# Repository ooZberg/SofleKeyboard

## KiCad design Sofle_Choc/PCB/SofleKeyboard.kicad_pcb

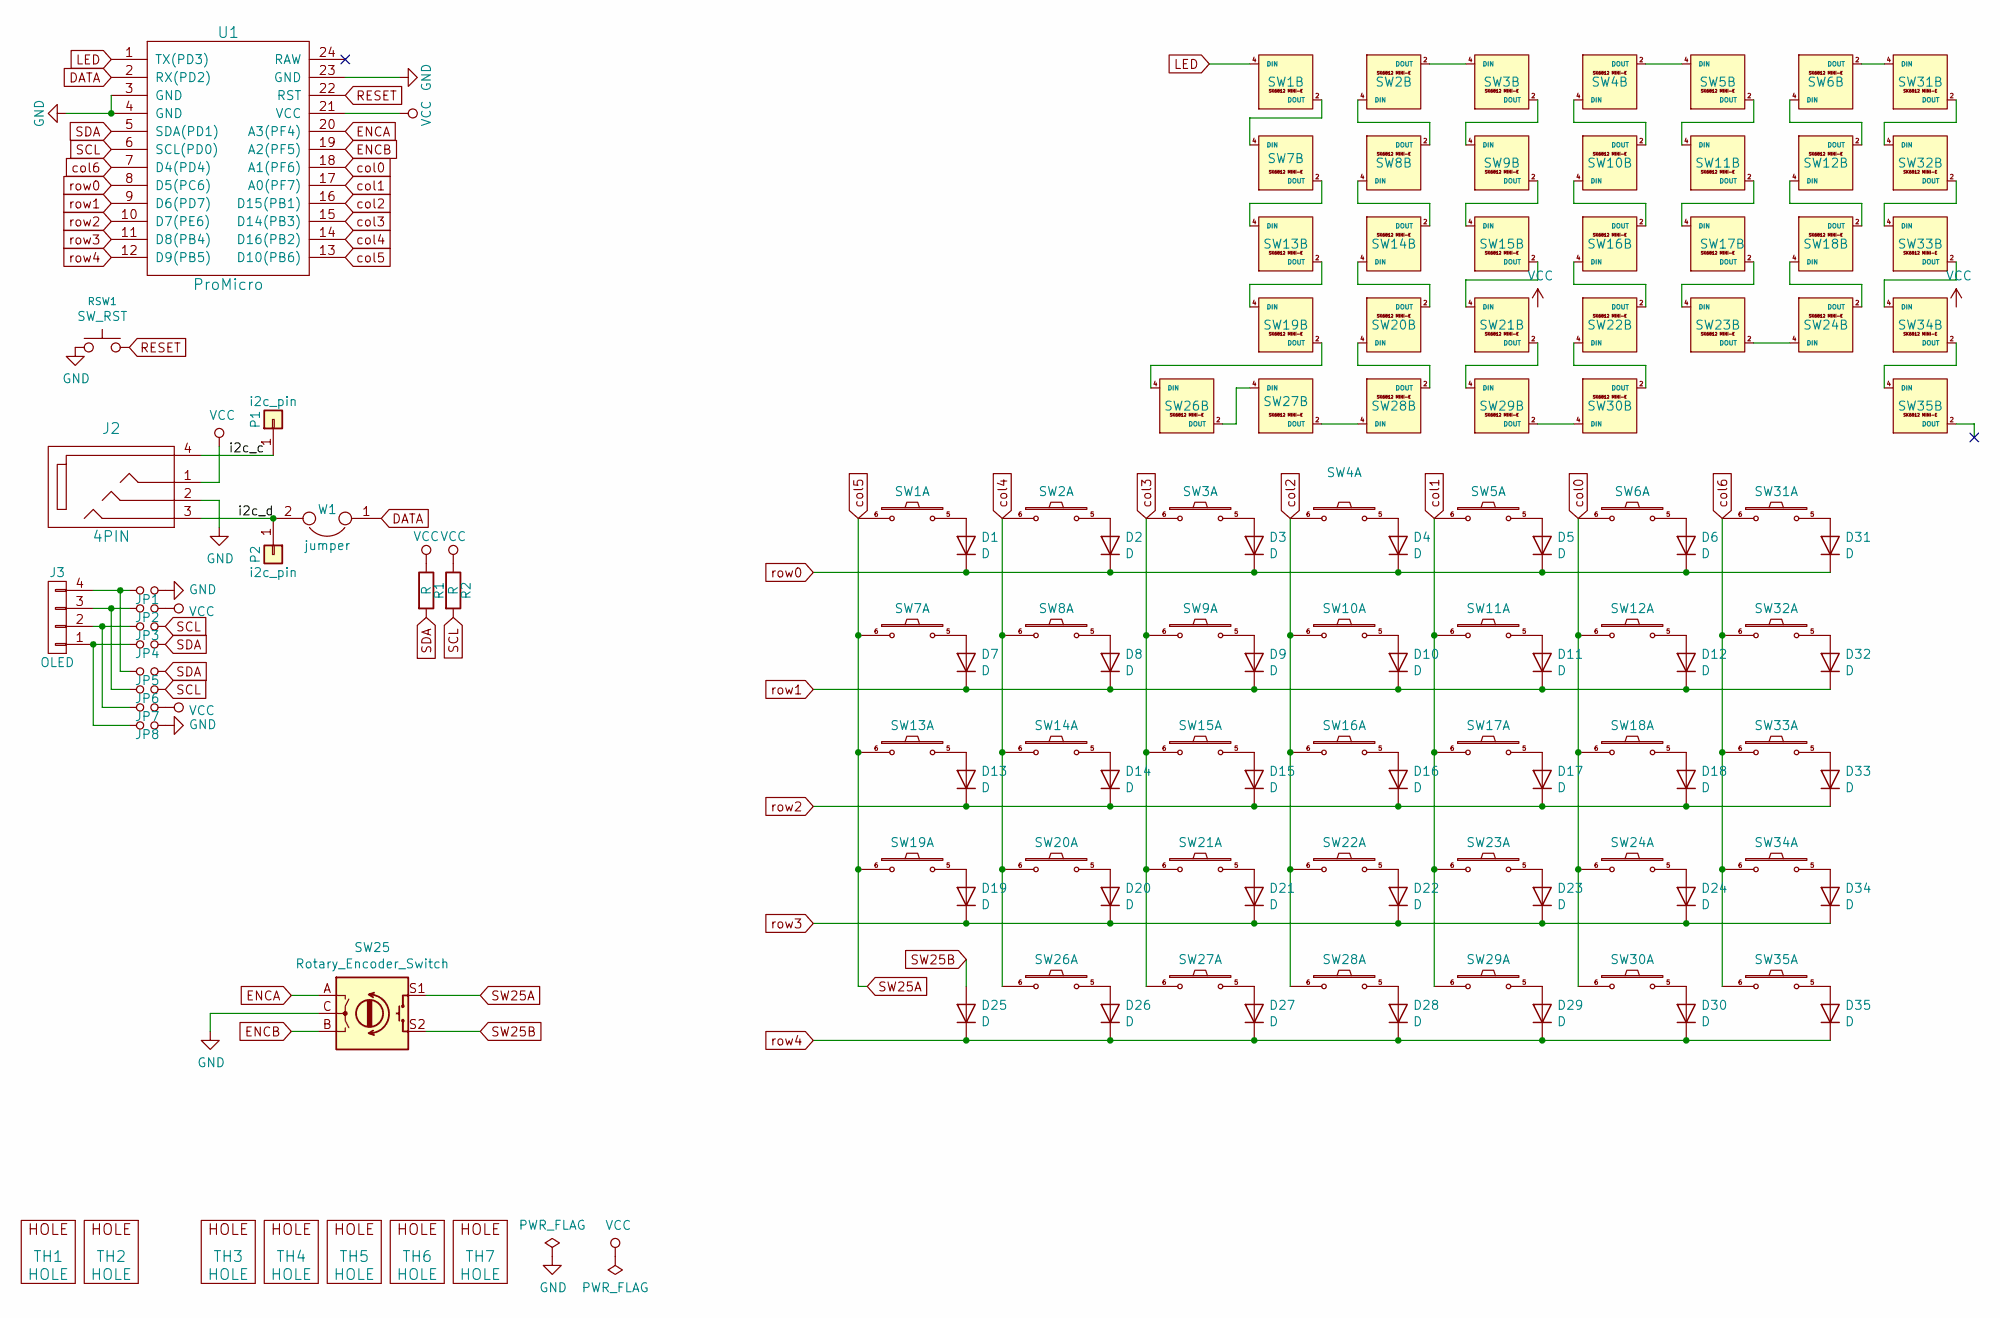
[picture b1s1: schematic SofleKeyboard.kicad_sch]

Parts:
D1, D2, D3, D4, D5, D6, D7, D8, D9, D10, D11, D12, D13, D14, D15, D16, D17, D18, D19, D20, D21, D22, D23, D24, D25, D26, D27, D28, D29, D30, D31, D32, D33, D34, D35: D; Diode_SOD123
J2: 4PIN; MJ-4PP-9
J3: OLED; OLED_4Pin
JP1, JP2, JP3, JP4, JP5, JP6, JP7, JP8: Jumper_NO_Small; Jumper
P1, P2: i2c_pin; 1pin_conn
R1, R2: R; RESISTOR_mini
RSW1: SW_RST; TACT_SWITCH_TVBP06
SW1, SW2, SW3, SW4, SW5, SW6, SW7, SW8, SW9, SW10, SW11, SW12, SW13, SW14, SW15, SW16, SW17, SW18, SW19, SW20, SW21, SW22, SW23, SW24, SW26, SW27, SW28, SW29, SW30, SW31, SW32, SW33, SW34, SW35: SW_PUSH_LED; Choc_Hotswap_SK6812MiniE
SW25: Rotary_Encoder_Switch; RotaryEncoder_Alps_EC11E-Switch_Vertical_H20mm-keebio_modif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
TH1, TH2: HOLE; M2_HOLE_PCB
TH3, TH4, TH5, TH6, TH7: HOLE; HOLE_M2_TH
U1: ProMicro
W1: jumper; jumper_data

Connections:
/i2c_c: J2.4, P1.1
/i2c_d: J2.3, P2.1, W1.2
DATA: U1.2 (RX(PD2)), W1.1
ENCA: SW25.A, U1.20 (A3(PF4))
ENCB: SW25.B, U1.19 (A2(PF5))
GND: J2.2, JP1.2, JP8.2, RSW1.1, SW1.3 (GND), SW2.3 (GND), SW3.3 (GND), SW4.3 (GND), SW5.3 (GND), SW6.3 (GND), SW7.3 (GND), SW8.3 (GND), SW9.3 (GND), SW10.3 (GND), SW11.3 (GND), SW12.3 (GND), SW13.3 (GND), SW14.3 (GND), SW15.3 (GND), SW16.3 (GND), SW17.3 (GND), SW18.3 (GND), SW19.3 (GND), SW20.3 (GND), SW21.3 (GND), SW22.3 (GND), SW23.3 (GND), SW24.3 (GND), SW25.C, SW26.3 (GND), SW27.3 (GND), SW28.3 (GND), SW29.3 (GND), SW30.3 (GND), SW31.3 (GND), SW32.3 (GND), SW33.3 (GND), SW34.3 (GND), SW35.3 (GND), U1.3 (GND), U1.4 (GND), U1.23 (GND)
LED: SW1.4 (DIN), U1.1 (TX(PD3))
unnamed: D1.2 (A), SW1.5
unnamed: D2.2 (A), SW2.5
unnamed: D3.2 (A), SW3.5
unnamed: D4.2 (A), SW4.5
unnamed: D5.2 (A), SW5.5
unnamed: D6.2 (A), SW6.5
unnamed: D7.2 (A), SW7.5
unnamed: D8.2 (A), SW8.5
unnamed: D9.2 (A), SW9.5
unnamed: D10.2 (A), SW10.5
unnamed: D11.2 (A), SW11.5
unnamed: D12.2 (A), SW12.5
unnamed: D13.2 (A), SW13.5
unnamed: D14.2 (A), SW14.5
unnamed: D15.2 (A), SW15.5
unnamed: D16.2 (A), SW16.5
unnamed: D17.2 (A), SW17.5
unnamed: D18.2 (A), SW18.5
unnamed: D19.2 (A), SW19.5
unnamed: D20.2 (A), SW20.5
unnamed: D21.2 (A), SW21.5
unnamed: D22.2 (A), SW22.5
unnamed: D23.2 (A), SW23.5
unnamed: D24.2 (A), SW24.5
unnamed: D26.2 (A), SW26.5
unnamed: D27.2 (A), SW27.5
unnamed: D28.2 (A), SW28.5
unnamed: D29.2 (A), SW29.5
unnamed: D30.2 (A), SW30.5
unnamed: D31.2 (A), SW31.5
unnamed: D32.2 (A), SW32.5
unnamed: D33.2 (A), SW33.5
unnamed: D34.2 (A), SW34.5
unnamed: D35.2 (A), SW35.5
unnamed: J3.1, JP4.1, JP8.1
unnamed: J3.2, JP3.1, JP7.1
unnamed: J3.3, JP2.1, JP6.1
unnamed: J3.4, JP1.1, JP5.1
unnamed: SW1.2 (DOUT), SW7.4 (DIN)
unnamed: SW2.4 (DIN), SW8.2 (DOUT)
unnamed: SW2.2 (DOUT), SW3.4 (DIN)
unnamed: SW3.2 (DOUT), SW9.4 (DIN)
unnamed: SW4.2 (DOUT), SW5.4 (DIN)
unnamed: SW10.4 (DIN), SW16.2 (DOUT)
unnamed: SW4.4 (DIN), SW10.2 (DOUT)
unnamed: SW5.2 (DOUT), SW11.4 (DIN)
unnamed: SW11.2 (DOUT), SW17.4 (DIN)
unnamed: SW12.4 (DIN), SW18.2 (DOUT)
unnamed: SW6.4 (DIN), SW12.2 (DOUT)
unnamed: SW7.2 (DOUT), SW13.4 (DIN)
unnamed: SW13.2 (DOUT), SW19.4 (DIN)
unnamed: SW14.4 (DIN), SW20.2 (DOUT)
unnamed: SW8.4 (DIN), SW14.2 (DOUT)
unnamed: SW9.2 (DOUT), SW15.4 (DIN)
unnamed: SW15.2 (DOUT), SW21.4 (DIN)
unnamed: SW16.4 (DIN), SW22.2 (DOUT)
unnamed: SW17.2 (DOUT), SW23.4 (DIN)
unnamed: SW18.4 (DIN), SW24.2 (DOUT)
unnamed: SW19.2 (DOUT), SW26.4 (DIN)
unnamed: SW20.4 (DIN), SW28.2 (DOUT)
unnamed: SW21.2 (DOUT), SW29.4 (DIN)
unnamed: SW22.4 (DIN), SW30.2 (DOUT)
unnamed: SW23.2 (DOUT), SW24.4 (DIN)
unnamed: SW26.2 (DOUT), SW27.4 (DIN)
unnamed: SW27.2 (DOUT), SW28.4 (DIN)
unnamed: SW29.2 (DOUT), SW30.4 (DIN)
unnamed: SW6.2 (DOUT), SW31.4 (DIN)
unnamed: SW31.2 (DOUT), SW32.4 (DIN)
unnamed: SW32.2 (DOUT), SW33.4 (DIN)
unnamed: SW33.2 (DOUT), SW34.4 (DIN)
unnamed: SW34.2 (DOUT), SW35.4 (DIN)
RESET: RSW1.2, U1.22 (RST)
SCL: JP3.2, JP6.2, R2.2, U1.6 (SCL(PD0))
SDA: JP4.2, JP5.2, R1.2, U1.5 (SDA(PD1))
SW25A: SW1.6, SW7.6, SW13.6, SW19.6, SW25.S1, U1.13 (D10(PB6))
SW25B: D25.2 (A), SW25.S2
VCC: J2.1, JP2.2, JP7.2, R1.1, R2.1, SW1.1 (VDD), SW2.1 (VDD), SW3.1 (VDD), SW4.1 (VDD), SW5.1 (VDD), SW6.1 (VDD), SW7.1 (VDD), SW8.1 (VDD), SW9.1 (VDD), SW10.1 (VDD), SW11.1 (VDD), SW12.1 (VDD), SW13.1 (VDD), SW14.1 (VDD), SW15.1 (VDD), SW16.1 (VDD), SW17.1 (VDD), SW18.1 (VDD), SW19.1 (VDD), SW20.1 (VDD), SW21.1 (VDD), SW22.1 (VDD), SW23.1 (VDD), SW24.1 (VDD), SW26.1 (VDD), SW27.1 (VDD), SW28.1 (VDD), SW29.1 (VDD), SW30.1 (VDD), SW31.1 (VDD), SW32.1 (VDD), SW33.1 (VDD), SW34.1 (VDD), SW35.1 (VDD), U1.21 (VCC)
col0: SW6.6, SW12.6, SW18.6, SW24.6, SW30.6, U1.18 (A1(PF6))
col1: SW5.6, SW11.6, SW17.6, SW23.6, SW29.6, U1.17 (A0(PF7))
col2: SW4.6, SW10.6, SW16.6, SW22.6, SW28.6, U1.16 (D15(PB1))
col3: SW3.6, SW9.6, SW15.6, SW21.6, SW27.6, U1.15 (D14(PB3))
col4: SW2.6, SW8.6, SW14.6, SW20.6, SW26.6, U1.14 (D16(PB2))
col6: SW31.6, SW32.6, SW33.6, SW34.6, SW35.6, U1.7 (D4(PD4))
row0: D1.1 (K), D2.1 (K), D3.1 (K), D4.1 (K), D5.1 (K), D6.1 (K), D31.1 (K), U1.8 (D5(PC6))
row1: D7.1 (K), D8.1 (K), D9.1 (K), D10.1 (K), D11.1 (K), D12.1 (K), D32.1 (K), U1.9 (D6(PD7))
row2: D13.1 (K), D14.1 (K), D15.1 (K), D16.1 (K), D17.1 (K), D18.1 (K), D33.1 (K), U1.10 (D7(PE6))
row3: D19.1 (K), D20.1 (K), D21.1 (K), D22.1 (K), D23.1 (K), D24.1 (K), D34.1 (K), U1.11 (D8(PB4))
row4: D25.1 (K), D26.1 (K), D27.1 (K), D28.1 (K), D29.1 (K), D30.1 (K), D35.1 (K), U1.12 (D9(PB5))

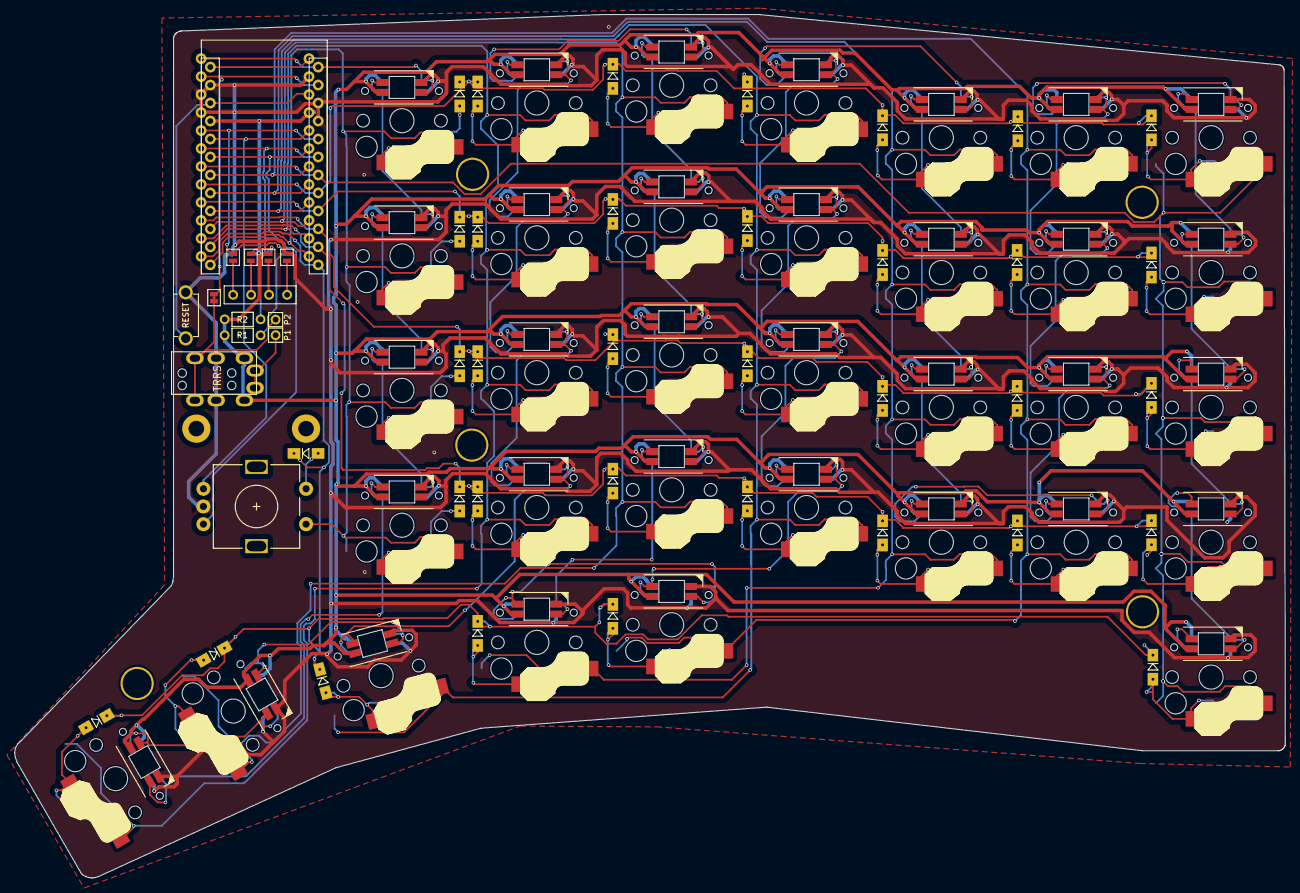
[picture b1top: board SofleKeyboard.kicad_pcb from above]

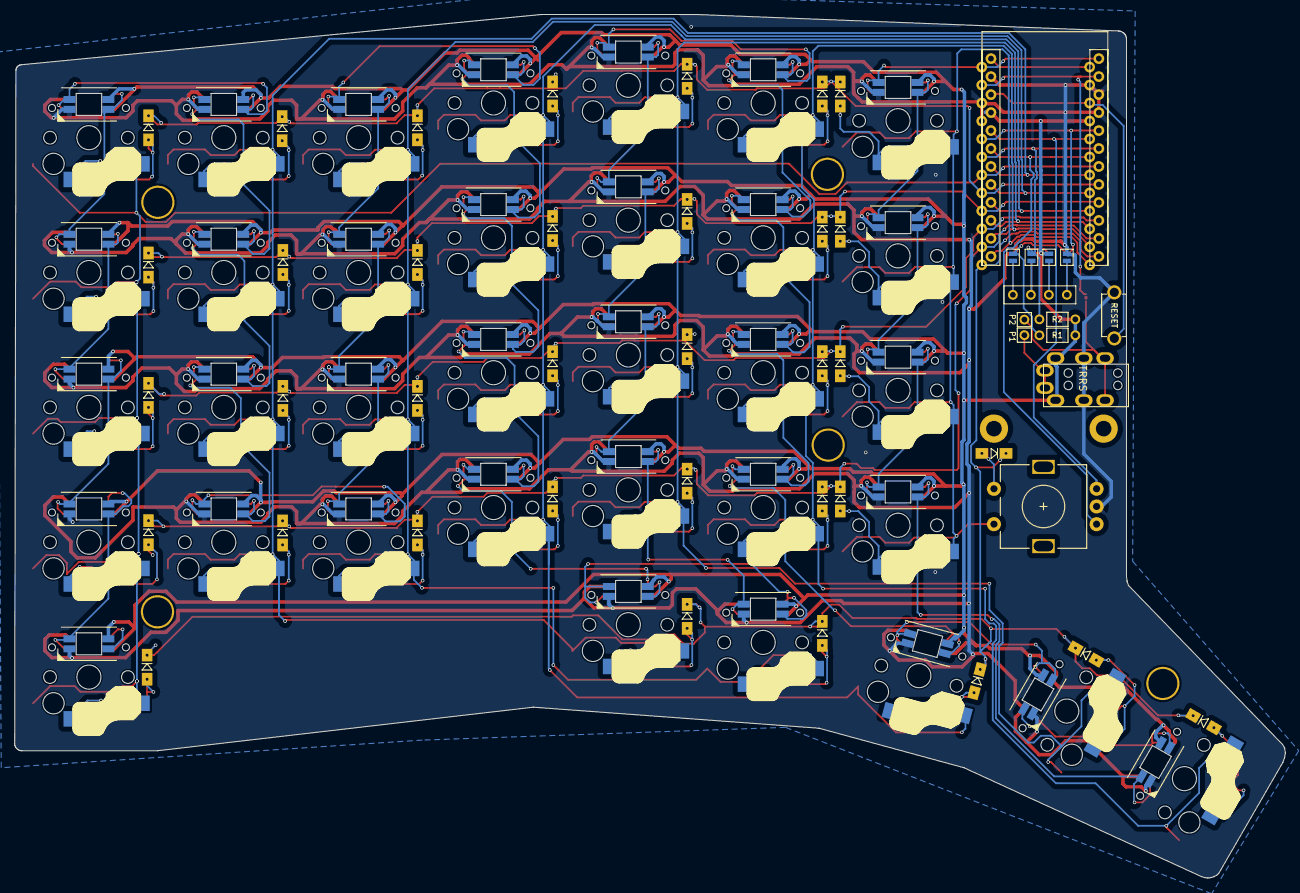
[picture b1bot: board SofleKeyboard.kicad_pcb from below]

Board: 2 copper layers, 179.5 x 122.0 mm, 94 parts (4 on the bottom side), 95 nets.

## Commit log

2024-01-23 Ignore lock files
2024-01-23 Fix footprints
2024-01-26 Add 7th row and move thumb cluster
2024-01-26 Fix routes
2024-01-27 Add routing
2024-01-27 Restore zones
2024-01-30 Make more space around diodes
2024-02-03 Increase via size and fix clearance
2024-02-04 Move mounting holes
2024-02-04 Make smooth edge cut corners
2024-02-04 Update top plate
